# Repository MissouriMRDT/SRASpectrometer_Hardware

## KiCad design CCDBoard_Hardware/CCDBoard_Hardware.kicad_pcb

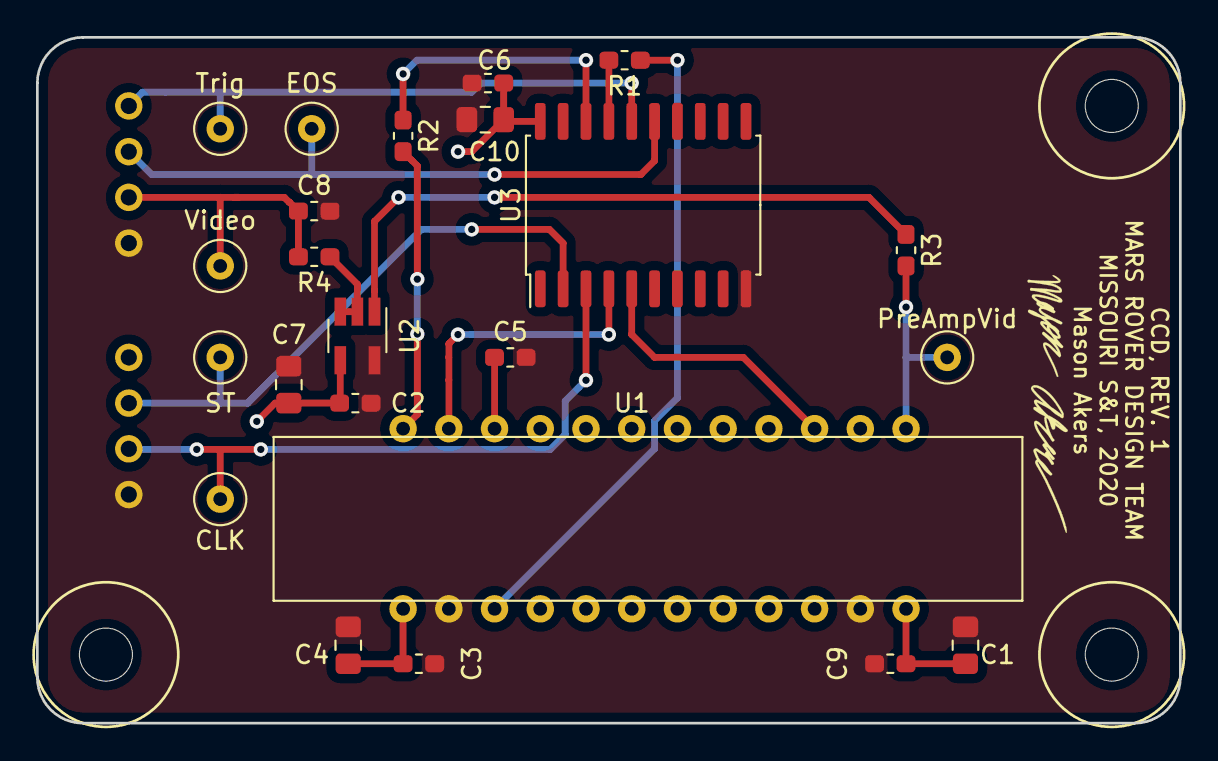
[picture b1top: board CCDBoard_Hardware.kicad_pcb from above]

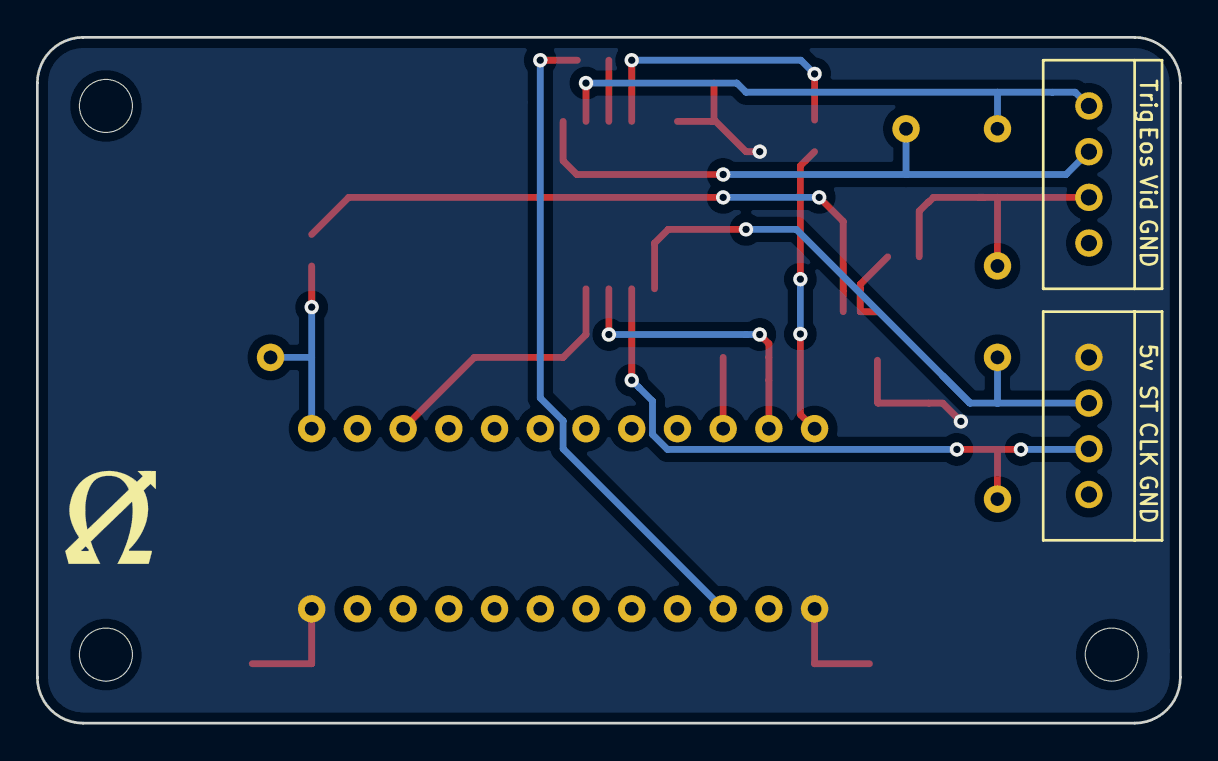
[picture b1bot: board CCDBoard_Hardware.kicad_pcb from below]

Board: 2 copper layers, 63.5 x 38.1 mm, 25 parts (2 on the bottom side), 17 nets.

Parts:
C1, C4, C7, C10: 22 µF/25 V; C_0805_2012Metric_Pad1.15x1.40mm_HandSolder
C2, C3, C6, C9: 0.1 µF; C_0603_1608Metric_Pad1.05x0.95mm_HandSolder
C5: 1 µF; C_0603_1608Metric_Pad1.05x0.95mm_HandSolder
C8: 22 pF; C_0603_1608Metric_Pad1.05x0.95mm_HandSolder
CLK: CLKTestPoint; TestPoint_THTPad_D2.5mm_Drill1.2mm
Conn1: Molex_SL_04 IN; MOLEX_SL_04_Vertical
Conn2: Molex_SL_04 OUT; MOLEX_SL_04_Vertical
EOS: EOSTestPoint; TestPoint_THTPad_D2.5mm_Drill1.2mm
PreAmpVid: VideoPreAmpTestPoint; TestPoint_THTPad_D2.5mm_Drill1.2mm
R1, R2: 82 Ω; R_0603_1608Metric_Pad1.05x0.95mm_HandSolder
R3: 100 Ω; R_0603_1608Metric_Pad1.05x0.95mm_HandSolder
R4: 51 Ω; R_0603_1608Metric_Pad1.05x0.95mm_HandSolder
ST: STTestPoint; TestPoint_THTPad_D2.5mm_Drill1.2mm
Trig: TrigTestPoint; TestPoint_THTPad_D2.5mm_Drill1.2mm
U1: S11639-01; CCD-S11639-01
U2: LT1818; SOT-23-5_HandSoldering
U3: 74HC541; SOIC-20W_7.5x12.8mm_P1.27mm
Video: VideoTestPoint; TestPoint_THTPad_D2.5mm_Drill1.2mm

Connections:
+5V: C1.1, C2.1, C3.1, C4.1, C6.1, C7.1, C9.1, C10.1, Conn1.1, U1.1, U1.12, U2.4, U3.20
CLK: CLK.1, Conn1.3, U3.3
CLK_IN: R1.2, U3.17
EOS: Conn2.2, EOS.1, U3.15
EOS_OUT: U1.15, U3.5
GND: C1.2, C2.2, C3.2, C4.2, C5.2, C6.2, C7.2, C8.2, C9.2, C10.2, Conn1.4, Conn2.4, U1.2, U1.11, U2.5, U3.10
unnamed: C5.1, U1.22
unnamed: R1.1, U1.3
unnamed: R2.2, U1.24
unnamed: R3.1, U2.1
unnamed: PreAmpVid.1, R3.2, U1.13
unnamed: R4.1, U2.2, U2.3
ST: Conn1.2, ST.1, U3.2
ST_IN: R2.1, U3.18
Trig: Conn2.1, Trig.1, U3.16
Trig_OUT: U1.23, U3.4
Video: C8.1, Conn2.3, R4.2, Video.1

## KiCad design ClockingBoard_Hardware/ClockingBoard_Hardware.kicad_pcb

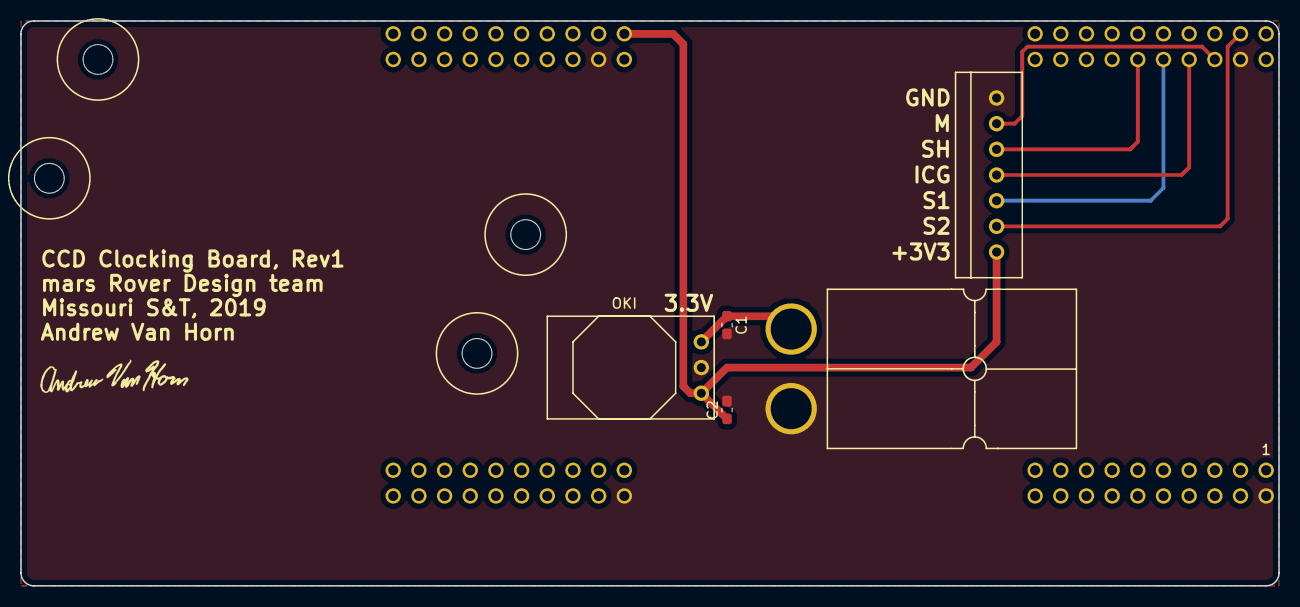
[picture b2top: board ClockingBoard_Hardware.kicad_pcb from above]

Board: 2 copper layers, 124.5 x 55.9 mm, 6 parts (0 on the bottom side), 8 nets.

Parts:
C1, C2: C; C_0603_1608Metric_Pad1.05x0.95mm_HandSolder
Conn1: AndersonPP; Anderson_2_Horizontal_Side_by_Side
Conn2: Molex_SL_07; MOLEX_SL_07_Vertical
U1: OKI; OKI_Horizontal
U2: TM4C129E_Launchpad; TM4C129E_Launchpad_FULL_THT_BOTTOM

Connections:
+3V3: C2.1, Conn2.1, U1.3, U2.+3V3'
/+12V: C1.1, Conn1.2, U1.1
GND: C1.2, C2.2, Conn1.1, Conn2.7, U1.2, U2.GND
ICG: Conn2.4, U2.PE1
M: Conn2.6, U2.PE0
SH: Conn2.5, U2.PE3
Sync1: Conn2.3, U2.PE2
Sync2: Conn2.2, U2.PE4

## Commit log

2018-10-20 Update gitignore
2019-03-09 created project
2019-03-09 Created CCD schematic
2019-03-09 Associated footprints and generated netlist
2019-03-09 updates Sensorboard connector
2019-03-12 Layout and step
2019-03-16 Creted Gerbs
2019-03-16 fixed gerbs
2019-03-16 Added silkscreen to CCD orientation
2019-10-05 Making new symbols and board for spec
2019-10-05 New shematic
    this might be completly wrong. IDK
2019-10-05 Redoing schematic for neatness
2019-10-05 Revision made. Much cleaner
2019-10-05 Fixed ground issues
2019-10-06 Redid Opamp and added testpoints
2019-10-06 Further Edits
2019-10-06 Added test points
2019-10-06 Created and assigned footprints
2019-10-06 Created new netlist
2019-10-07 ratsnest
    I may be doing this wrong. go back to this commit to check.
2019-10-07 Maybe a good start
2019-10-07 maybe
2019-10-07 connected testpoints
2019-10-08 doing stuff to make it not awful
2019-10-08 Ratsnest is accurate follow it
2019-10-08 needs reformat
2019-10-10 Not an awful design
    damn you clocking trace! *Shaking fist*
2019-10-10 not bad
2019-10-11 Finished
    thank god
2019-10-12 added silk screens
2019-10-12 final updates
2019-10-15 improvements that might break things
2019-10-15 same as the last. please dont be broken
2019-10-15 Revert "improvements that might break things"
    This reverts commit 929e755a3a655d7aa2cd30a99533c48bf9da1e19.
2019-10-15 Revert "Revert "improvements that might break things""
    This reverts commit d5188e1fd330cde9b95ae0a822a42f7003dfe195.
2019-10-16 Why you no work.
    for the love of god
2019-10-16 I swear to god github
2019-10-20 Added laser diode breakout
2019-10-20 made laser have curved edges
2019-10-20 Fixed edgecut and regen gerbs
2019-10-20 Fixed edgecut
